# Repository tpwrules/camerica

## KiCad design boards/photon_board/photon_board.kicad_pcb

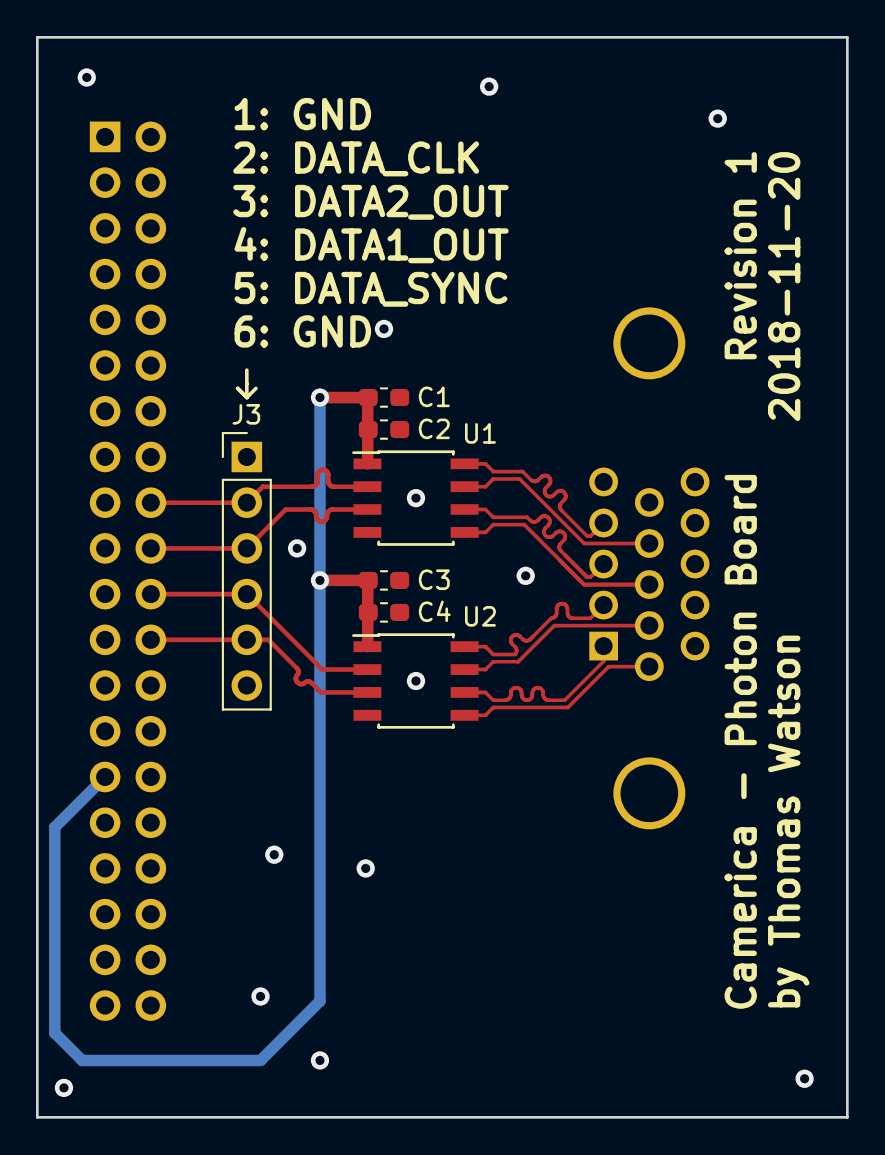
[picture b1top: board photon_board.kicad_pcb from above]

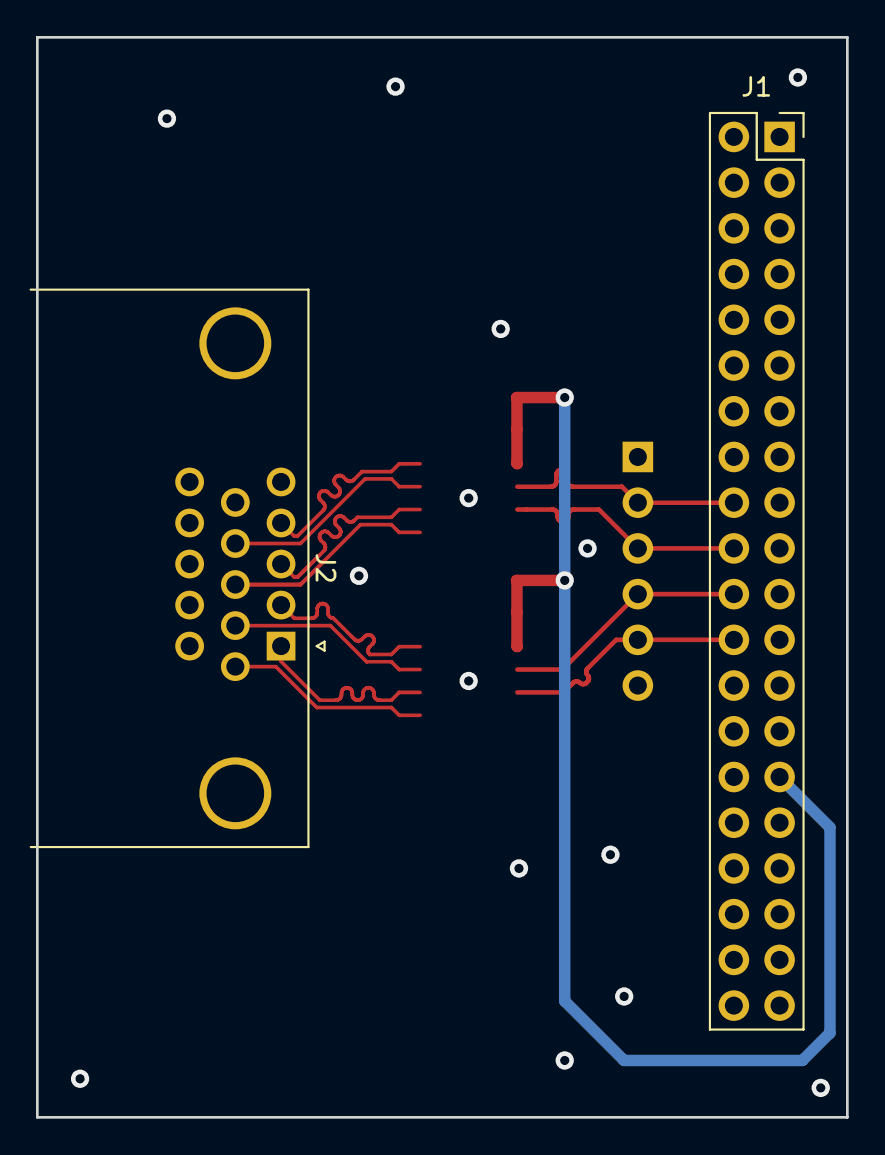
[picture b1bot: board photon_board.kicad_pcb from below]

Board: 2 copper layers, 45.0 x 60.0 mm, 9 parts (2 on the bottom side), 14 nets.

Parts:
C1, C3: 1u; C_0603_1608Metric_Pad1.05x0.95mm_HandSolder
C2, C4: 0.1u; C_0603_1608Metric_Pad1.05x0.95mm_HandSolder
J1: TERASIC; PinSocket_2x20_P2.54mm_Vertical
J2: PHOTON; DSUB-15-HD_Female_Horizontal_Pitch2.28x2.54mm_EdgePinOffset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
J3: DATA; PinHeader_1x06_P2.54mm_Vertical
U1, U2: SN65LVDT34D; SOIC-8_3.9x4.9mm_P1.27mm

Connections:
+3V3: C1.1, C2.2, C3.1, C4.2, J1.29, U1.1, U2.1
/DATA1_OUT: J1.22, J3.4, U2.2
/DATA1_OUT+: J2.2, U2.8
/DATA1_OUT-: J2.7, U2.7
/DATA2_OUT: J1.20, J3.3, U1.3
/DATA2_OUT+: J2.3, U1.6
/DATA2_OUT-: J2.8, U1.5
/DATA_CLK: J1.18, J3.2, U1.2
/DATA_CLK+: J2.4, U1.8
/DATA_CLK-: J2.9, U1.7
/DATA_SYNC: J1.24, J3.5, U2.3
/DATA_SYNC+: J2.1, U2.6
/DATA_SYNC-: J2.6, U2.5
GND: C1.2, C2.1, C3.2, C4.1, J1.12, J1.30, J2.0, J2.10, J3.1, J3.6, U1.4, U2.4

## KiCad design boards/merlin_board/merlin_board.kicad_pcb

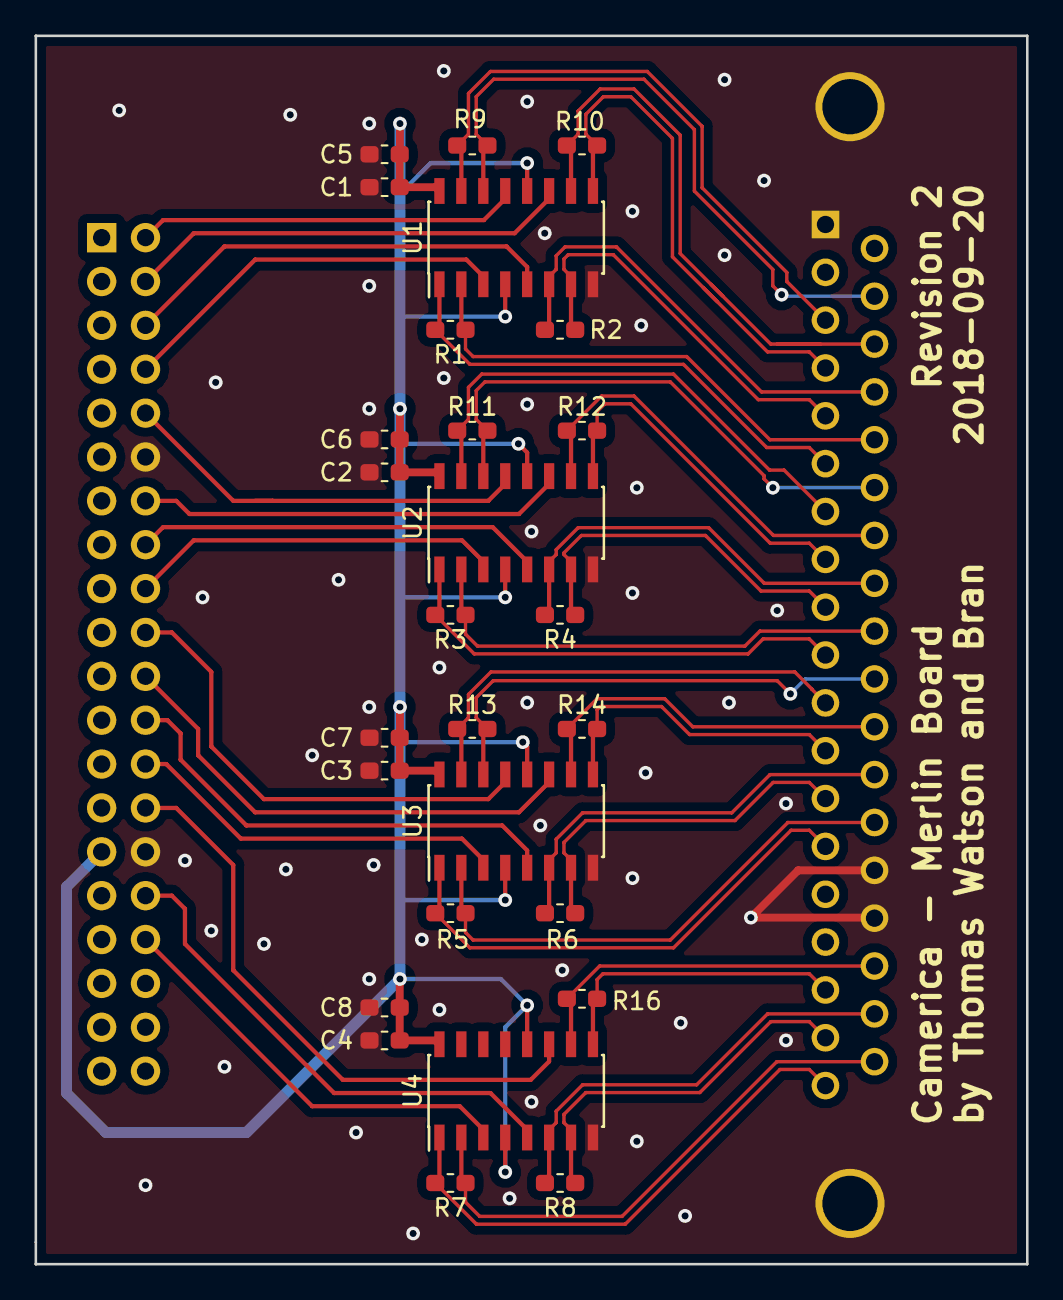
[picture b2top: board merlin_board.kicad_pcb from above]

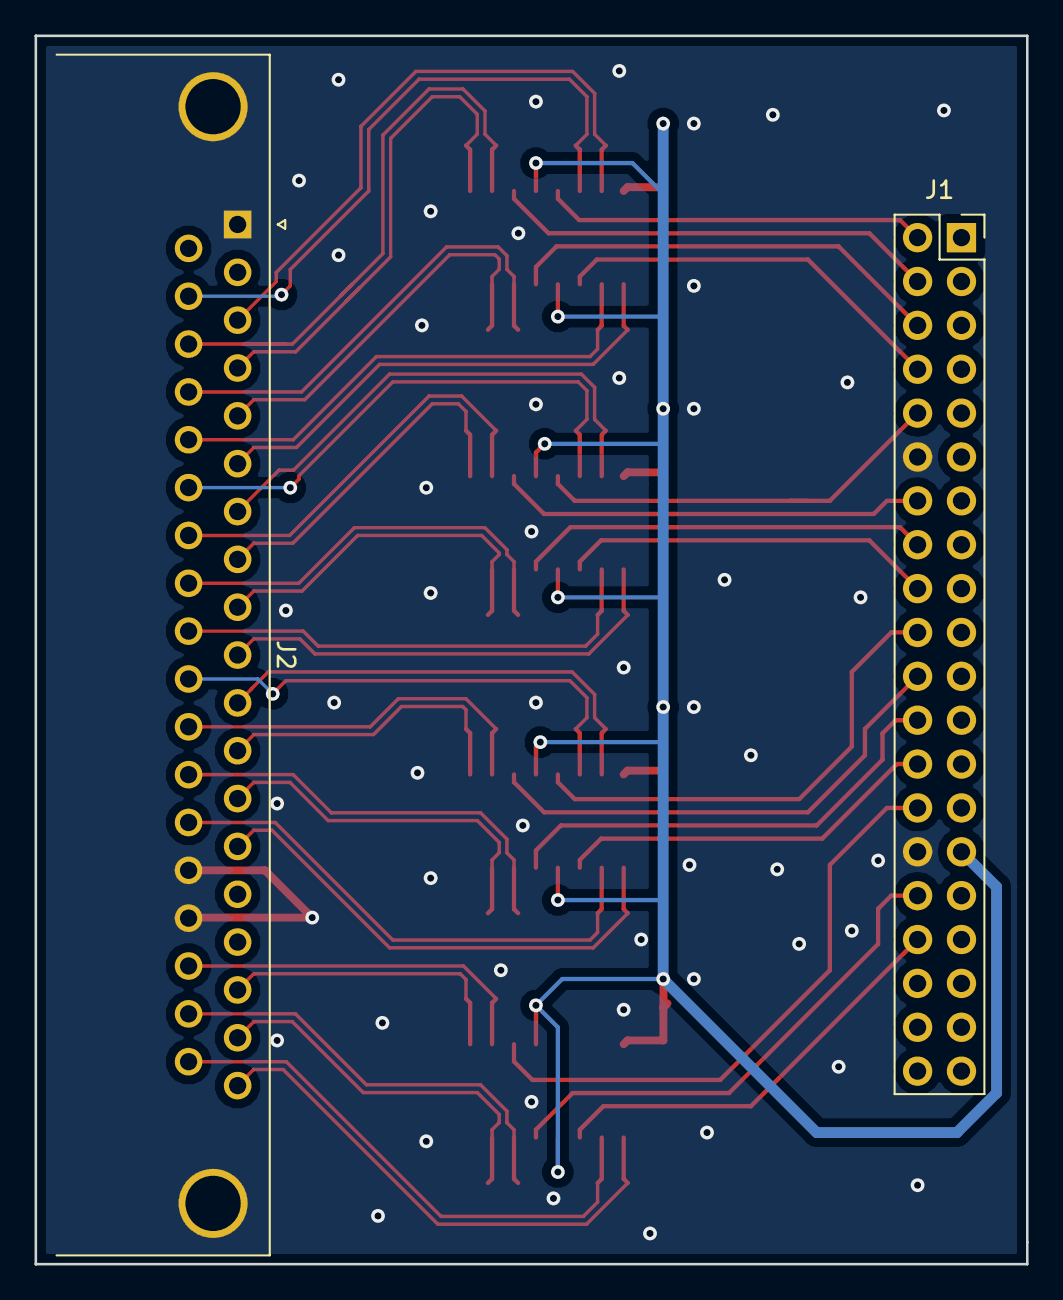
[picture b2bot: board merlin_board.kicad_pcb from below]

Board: 2 copper layers, 57.4 x 71.1 mm, 29 parts (2 on the bottom side), 47 nets.

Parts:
C1, C2, C3, C4: 100n; C_0603_1608Metric_Pad1.05x0.95mm_HandSolder
C5, C6, C7, C8: 1u; C_0603_1608Metric_Pad1.05x0.95mm_HandSolder
J1: TERASIC; PinSocket_2x20_P2.54mm_Vertical
J2: CAMERA; DSUB-37_Male_Horizontal_P2.77x2.84mm_EdgePinOffset7.70mm_Ho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
R1, R2, R3, R4, R5, R6, R7, R8, R9, R10, R11, R12, R13, R14, R16: 120; R_0603_1608Metric_Pad1.05x0.95mm_HandSolder
U1, U2, U3, U4: MAX3094; SOIC-16_3.9x9.9mm_P1.27mm

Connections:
+3V3: C1.2, C2.2, C3.2, C4.2, C5.2, C6.2, C7.2, C8.2, J1.29, U1.4, U1.12, U1.16, U2.4, U2.12, U2.16, U3.4, U3.12, U3.16, U4.4, U4.12, U4.16
/B00: J1.2, U1.13
/B00N: J2.3, R9.2, U1.15
/B00P: J2.21, R9.1, U1.14
/B01: J1.4, U1.11
/B01N: J2.4, R10.1, U1.9
/B01P: J2.22, R10.2, U1.10
/B02: J1.6, U1.5
/B02N: J2.5, R2.1, U1.7
/B02P: J2.23, R2.2, U1.6
/B03: J1.8, U1.3
/B03N: J2.6, R1.2, U1.1
/B03P: J2.24, R1.1, U1.2
/B04: J1.10, U2.13
/B04N: J2.7, R11.2, U2.15
/B04P: J2.25, R11.1, U2.14
/B05: J1.14, U2.11
/B05N: J2.8, R12.1, U2.9
/B05P: J2.26, R12.2, U2.10
/B06: J1.16, U2.5
/B06N: J2.9, R4.1, U2.7
/B06P: J2.27, R4.2, U2.6
/B07: J1.18, U2.3
/B07N: J2.10, R3.2, U2.1
/B07P: J2.28, R3.1, U2.2
/B08: J1.20, U3.13
/B08N: J2.11, R13.2, U3.15
/B08P: J2.29, R13.1, U3.14
/B09: J1.22, U3.11
/B09N: J2.12, R14.1, U3.9
/B09P: J2.30, R14.2, U3.10
/B10: J1.24, U3.5
/B10N: J2.13, R6.1, U3.7
/B10P: J2.31, R6.2, U3.6
/B11: J1.26, U3.3
/B11N: J2.14, R5.2, U3.1
/B11P: J2.32, R5.1, U3.2
/CLOCK: J1.34, U4.3
/CLOCKN: J2.19, R7.2, U4.1
/CLOCKP: J2.37, R7.1, U4.2
/HSYNC: J1.32, U4.5
/HSYNCN: J2.18, R8.1, U4.7
/HSYNCP: J2.36, R8.2, U4.6
/VSYNC: J1.28, U4.11
/VSYNCN: J2.17, R16.1, U4.9
/VSYNCP: J2.35, R16.2, U4.10
GND: C1.1, C2.1, C3.1, C4.1, C5.1, C6.1, C7.1, C8.1, J1.12, J1.30, J2.0, J2.1, J2.33, J2.34, U1.8, U2.8, U3.8, U4.8

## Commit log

2018-08-20 first commit of fpga stuff
2018-08-20 ignore generated fpga files
2018-08-20 remove cruft from system
2018-08-21 set up proto hardware for dram test
2018-08-21 more trash
2018-08-21 connect interrupts to nios so bsp doesnt whine
2018-08-21 set up nios template
2018-08-22 software necessary for demonstration
2018-08-22 get logic analyzer capture of camera bus
2018-08-22 back-annotate to clear up warnings about crap
2018-08-22 add clock definition for camera bus
2018-08-22 work on revamping logic to use standard blocks
2018-08-24 fix misc syntax errors so analysis actually works
2018-08-24 get rid of intel video reader cause it costs money
2018-08-24 write module to bring camera in
2018-08-24 generate megafunctions to store the buffers
2018-08-30 fix timing in cambus and clarify output parameters
2018-08-31 update ram IP to actually be good
2018-08-31 start on the actual linereader engine incl mem read
2018-08-31 delay pixel by 1 camera clock to make linereader easier
2018-09-04 add state machine to actually capture the frames
2018-09-05 add histogram state machine too
2018-09-05 do register r/w logic
2018-09-05 edit makefile to avoid scrubbing away camerica source
2018-09-05 add program to test a register from hps
2018-09-05 add library to fiddle with hw registers in python
2018-09-05 rewrite nios code to work with new architecture
2018-09-07 do enough to get frames out of the machine and into a file
2018-09-08 remember to flush cpu cache before reading frames
2018-09-08 wait for hsync and vsync to be oppositely-asserted so lines/frames don't get duplicated
2018-09-08 add garbage file viewer just for testing porpoises
2018-09-08 bulk replace tabs with spaces in python files
2018-09-08 remove old commented out code from uc code
2018-09-08 fix addressing issue with even lines/odd frames
2018-09-08 fix vid mem logic issue causing duplicate pixels
2018-09-08 make vidshow 2x and also dump a png for external testing
2018-09-08 frame height is definitely 256 lines
2018-09-18 redo cambus in a cleaner way to avoid sync issues
2018-09-18 fix ring buffer in nios so it's not 16 frames behind
2018-09-18 prevent weird frames when dma starts
2018-09-19 fix potential issue with vid mem read from different areas
2018-09-19 fix histogram to include last pixel of line
2018-09-19 initialize nios_program with the nios program
2018-09-19 remove debugging and other junk from nios code
2018-09-19 remove nios jtag uart and shrink nios memory by removing drivers
2018-09-20 dump histograms to stdout also to check
2018-09-20 start frame counter at 0 every time dma is started
2018-09-20 write compressed and chukned and seekable and etc video files
2018-09-27 remove compression but leave option available
2018-09-27 avoid holding onto buffer longer than necessary when writing
2018-09-27 add random id to vidfiles so that all of the same video have the same id
2018-09-27 write number of frames in each chunk to index too
2018-09-27 add not tested and kinda broken but working reader
2018-10-01 start work on studio program to do everything
2018-10-01 add basic display of the histogram
2018-10-01 expand histogram 2x and center it
2018-10-01 add ability to slide around visible window on histogram
2018-10-01 add extremely bad test record handler
2018-10-04 fix a couple issues and try to speed things up
2018-10-04 upgrade histogram to 512 entries and linebuffer to max 1024 pixels
2018-10-04 add terrible mode selection
2018-10-04 add video reading and seeking
2018-10-18 improve histogram scaling accuracy
2018-10-18 rework vidfile so files are always uncompressed and seeking is easy
2018-10-19 fix end of file read handling and also some seek stuff
2018-10-19 add frame step arrow keys
2018-10-19 fix some issues with seeking logic and rework frame counter
2018-10-19 improve shutdown and error handling
2018-10-19 flip histogram traditional side up
2018-10-19 show selected area of histogram in more obvious way
2018-10-19 definitely stop
2018-10-19 rename playback command to play so it sounds verbier
2018-10-19 show selection of lowest bin in histo
2018-10-19 remove stack tracing stuff
2018-10-22 add test arm asm routine
2018-10-22 draw screen with ARM NEON extensions for turbo speeeeeeeed
2018-10-22 clean up ignoring
2018-10-23 refactor drawing logic into its own class so it can be upgraded later
2018-10-23 add kind of lame average draw time stat
2018-10-23 tie neon routines in
2018-10-23 improve neon efficiency
2018-10-25 widen display area to make room for status texts
2018-10-25 show some basic statuses
2018-10-25 restructure frame counters to make sense
2018-10-25 show first frame when playback is initialized, instead of random memory garbage
2018-10-25 display disk buffer full percentage
2018-10-25 improve how UI works with new, in progress classes
2018-10-25 allow movement of histogram edges with mouse
2018-10-25 improve histogram movement feel
2018-10-31 add merlin board files
2018-10-31 yay macos
2018-10-31 start out board for photon camera
2018-10-31 add connectors
2018-11-01 add custom lvds receiver symbol
2018-11-01 finalize schematic
2018-11-06 add seek bar
2018-11-20 add connector for photon and make appropriate footprint
2018-11-20 add data out connector for eg logic analysis
2018-11-20 route board
2018-11-20 do up silkscreen
2018-11-26 rework dma status to solve issue where dma couldn't shut down if camera was off
2018-12-06 upgrade datapath to 16 bits for future expansion
2018-12-06 remove vestiges of unused and silly features
2018-12-10 fix randomly corrupting HPS memory by turnig off DMA when not in use and not violating external bus spec
2018-12-10 add camera type register for switching the attached camera
2018-12-10 implement camera type system for merlin
2018-12-10 add first approxmiation photon support
2018-12-11 replace single hongo dma buffer with one per frame and increase number and size for bigger camera
2018-12-12 encapsulate camera parameters in object instead of hardcoding them everywhere
2018-12-12 correctly add photon support
2018-12-12 add neon drawing routine for photon
2018-12-12 fix recording and playback
2018-12-13 fix photon timing and clock assignments
2019-03-23 add kernel customizations
2019-03-23 add built kernel and modules
2019-03-23 move kernel build files to build directory
2019-03-23 add script to update fpga and latest fpga config zip
2019-03-23 add system start/stop scripts
2019-03-23 update prebuilt linux pieces to ones that work
2019-03-23 sysup calls sysdown correctly
2019-03-23 build fuse module into kernel and also add cifs into kernel
2019-03-23 include all kernel modules so the kernel actually gets installed correctly
2019-03-24 work on splash screen
2019-03-24 adjust keming of Studio and add github URL to splash
2019-03-24 remove old and test files
2019-03-24 improve performance in histo and frame grabbing
2019-03-24 use tkwidgets to ask the user which camera is attached
2019-03-24 display splash screen first thing
2019-03-24 actually detect if camerica hardware is present
2019-03-24 remove vestiges of old dma buf writing method
2019-03-24 add infrastructure for mode changing and basic test
2019-03-24 auto switch to live mode if started with hardware
2019-03-24 fix glitch at bottom of histogram
2019-03-24 make cancelling the hardware setup dialog work correctly
2019-03-24 add keyboard control of all modes
2019-03-24 save camera type in vidfile so the user doesn't have to select the right type on playback
2019-03-24 dynamically change status texts with mode
2019-03-24 be more clear about 'nothing active' mode
2019-03-24 fix some bounding issues with widgets
2019-03-24 add janky button
2019-03-24 only listen to left clicks
2019-03-24 add meaningless buttons to change mode and select camera
2019-03-24 make buttons prettier and more efficient
2019-03-24 give buttons an enabled and disabled state
2019-03-24 enable and disable buttons as appropriate
2019-03-24 unify buttons and key commands
2019-03-24 fix latent camera when playing back with no hardware
2019-03-24 make sure splash gets the love it deserves
2019-03-24 hide pygame's boot message
2019-03-24 allow user to cancel file dialogs
2019-03-24 add automatic histogram function
2019-03-24 change idle mode to stop
2019-03-25 add fpga configuration output to repo
2019-03-25 add new file to install all the kernel and fpga stuff at once
2019-03-25 install components needs to rebuild the neon bit
2019-03-25 add updater which automatically pulls the repo and installs components if necessary
2019-03-25 auto mount USB device on sysup
2019-03-25 better error handling and status on sysup and down
2019-03-25 make sure splash screen redraws while you wait
2019-03-25 spruce up open and save file dialogs
2019-03-25 make sure ko directory exists so install components works on first run
2019-03-25 automatically create symlinks on desktop when installing components
2019-03-25 even if they don't already exist
2019-03-25 rebuild fpga config with new toolchain setup just to make sure it works. should be no changes
2019-04-04 put digikey links on merlin board schematic
